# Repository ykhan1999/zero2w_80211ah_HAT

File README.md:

# zero2w_80211ah_HAT
PCB design files for a module that allows interfacing the Raspberry Pi SBC products with the Heltec HT-HC01P module.  

Files were prepared using KiCad 9.0 and are available under the CERN-OHL-S license.

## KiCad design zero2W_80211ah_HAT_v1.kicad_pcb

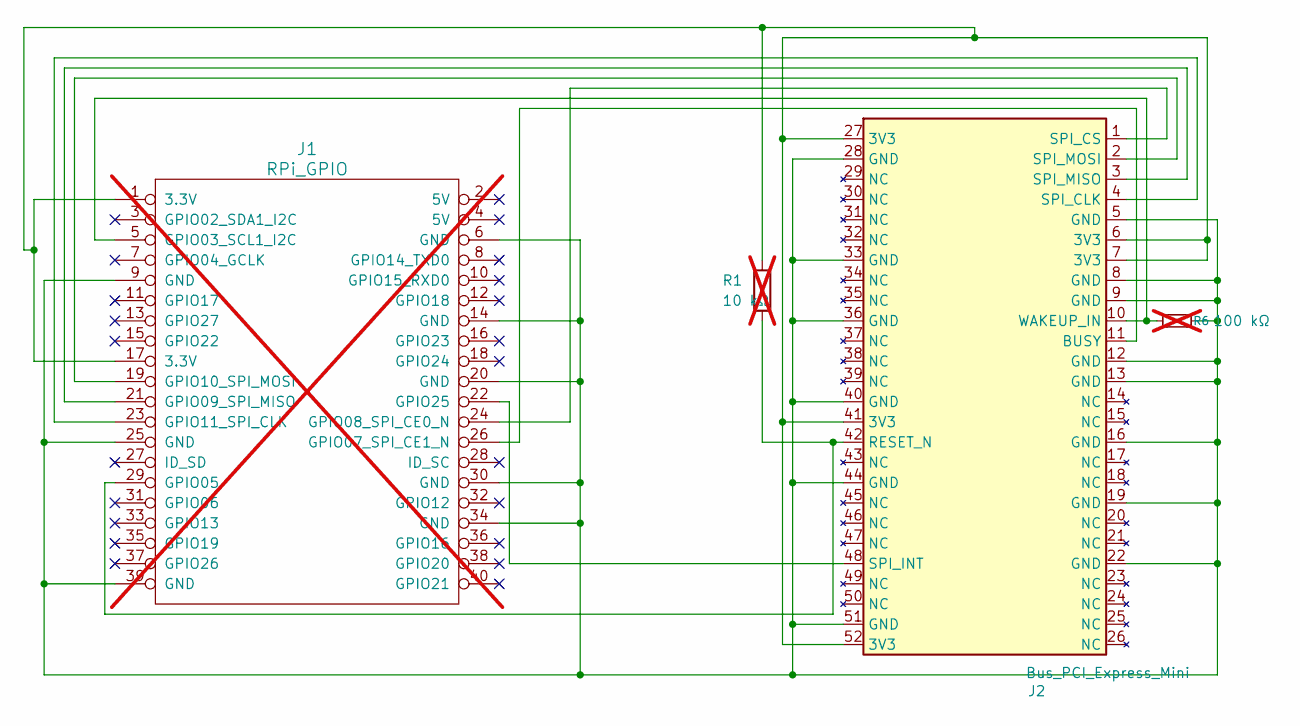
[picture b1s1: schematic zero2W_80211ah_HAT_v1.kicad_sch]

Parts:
J1: RPi_GPIO; PinSocket_2x20_P2.54mm_Vertical; not fitted
J2: Bus_PCI_Express_Mini; CONN60_2041262-1_TEC
R1: 10 kΩ; R_0402_1005Metric; not fitted
R6: 100 kΩ; R_0402_1005Metric; not fitted

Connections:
unnamed: J1.1 (3.3V), J1.17 (3.3V), J2.6 (3V3), J2.7 (3V3), J2.27 (3V3), J2.41 (3V3), J2.52 (3V3), R1.1
unnamed: J1.6 (GND), J1.9 (GND), J1.14 (GND), J1.20 (GND), J1.25 (GND), J1.30 (GND), J1.34 (GND), J1.39 (GND), J2.5 (GND), J2.8 (GND), J2.9 (GND), J2.12 (GND), J2.13 (GND), J2.16 (GND), J2.19 (GND), J2.22 (GND), J2.28 (GND), J2.33 (GND), J2.36 (GND), J2.40 (GND), J2.44 (GND), J2.51 (GND), R6.2
unnamed: J1.5 (GPIO03_SCL1_I2C), J2.10 (WAKEUP_IN), R6.1
unnamed: J1.29 (GPIO05), J2.42 (RESET_N), R1.2
unnamed: J1.26 (GPIO07_SPI_CE1_N), J2.11 (BUSY)
unnamed: J1.24 (GPIO08_SPI_CE0_N), J2.1 (SPI_CS)
unnamed: J1.21 (GPIO09_SPI_MISO), J2.3 (SPI_MISO)
unnamed: J1.19 (GPIO10_SPI_MOSI), J2.2 (SPI_MOSI)
unnamed: J1.23 (GPIO11_SPI_CLK), J2.4 (SPI_CLK)
unnamed: J1.22 (GPIO25), J2.48 (SPI_INT)

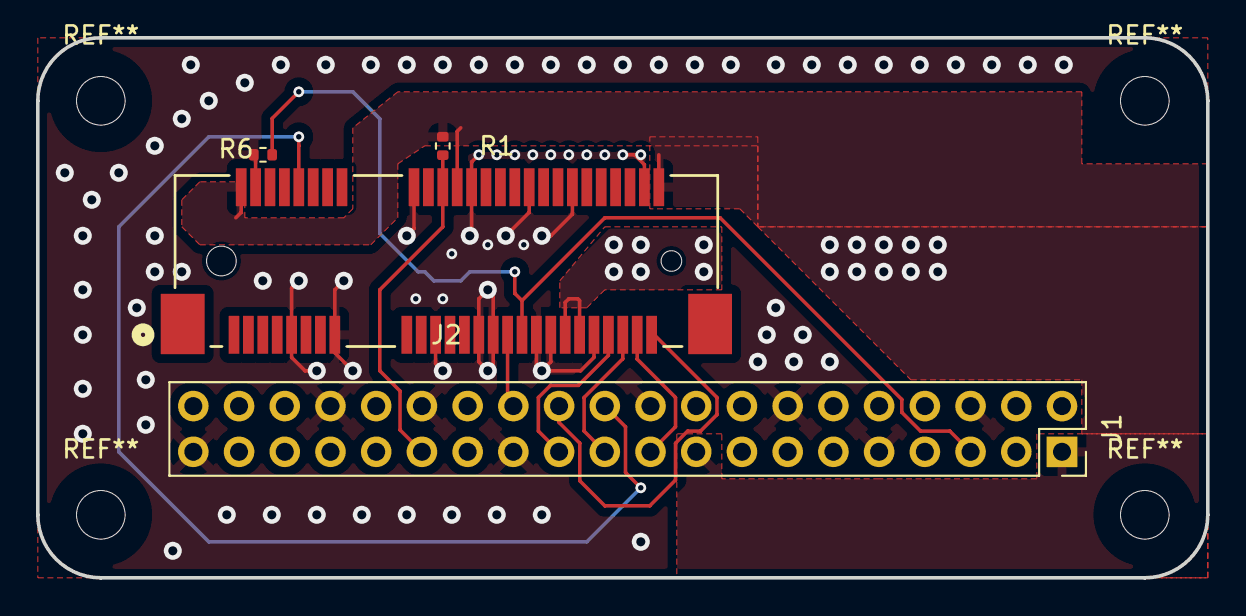
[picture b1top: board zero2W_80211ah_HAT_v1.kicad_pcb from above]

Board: 2 copper layers, 65.0 x 30.0 mm, 4 parts (0 on the bottom side), 10 nets.

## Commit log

2026-01-03 add license
2026-01-03 add readme
